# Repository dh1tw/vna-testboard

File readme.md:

# VNA Testboard PCB

I really like this small PCB testboard for prototyping and experimenting with my Vector Network Analyzers. [SDR-Kits](https://www.sdr-kits.net) used to sell it as a complimentary item for the DG8SAQ VNA. Unfortunately, mine showed some wear and SDR-Kits doesn't sell the PCB / Testkit anymore. So I clone it.

## Layout

## Design considerations

The PCB was designed in KiCad 7. You will most likely have to **change / adopt the SMA connectors** since I used a couple of non-standard ones which, I just had in stock.

I designed the traces as microstrip lines, matching 50 Ohm. This resulting trace width is 1.85mm using __1,0mm PCB thickness__ and an Epsilon r = 4.5 of the FR4 material. I get accurate results up to a few hundred Megahertz.

The pin sockets have a 2.54mm spacing.

I use Nylon M3 screws & nuts as feet.

## License

[Creative Commons Attribution-ShareAlike 4.0 International](https://creativecommons.org/licenses/by-sa/4.0/deed.en)

## This means you are free to:

- **Share** - copy and redistribute the material in any medium or format
- **Adapt** - remix, transform, and build upon the material for any purpose, even commercially

## under the following terms:

- **Attribution** - You must give appropriate credit, provide a link to the license, and indicate if changes were made. You may do so in any reasonable manner, but not in any way that suggests the licensor endorses you or your use.
- **ShareAlike** - If you remix, transform, or build upon the material, you must distribute your contributions under the same license as the original.

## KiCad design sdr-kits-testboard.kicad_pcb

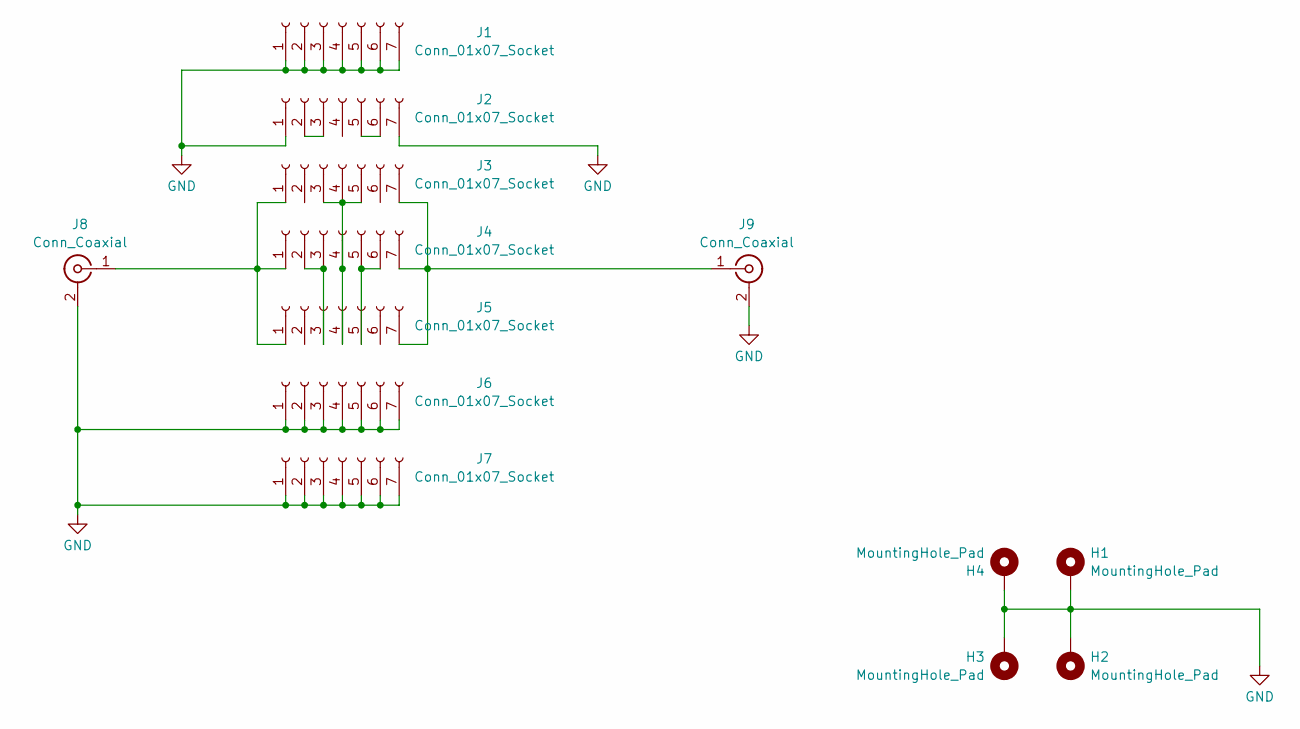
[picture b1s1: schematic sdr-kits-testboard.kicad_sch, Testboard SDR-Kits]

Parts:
H1, H2, H3, H4: MountingHole_Pad; MountingHole_3.2mm_M3_DIN965_Pad
J1, J2, J3, J4, J5, J6, J7: Conn_01x07_Socket; PinSocket_1x07_P2.54mm_Vertical_SDR-Kits
J8, J9: Conn_Coaxial; SMA_Aliexpress_EdgeMount

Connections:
GND: H1.1, H2.1, H3.1, H4.1, J1.1, J1.2, J1.3, J1.4, J1.5, J1.6, J1.7, J2.1, J2.7, J6.1, J6.2, J6.3, J6.4, J6.5, J6.6, J6.7, J7.1, J7.2, J7.3, J7.4, J7.5, J7.6, J7.7, J8.2 (Ext), J9.2 (Ext)
unnamed: J2.2, J2.3
unnamed: J2.5, J2.6
unnamed: J3.1, J4.1, J5.1, J8.1 (In)
unnamed: J3.3, J3.4, J3.5, J4.4, J5.4
unnamed: J3.7, J4.7, J5.7, J9.1 (In)
unnamed: J4.2, J4.3, J5.3
unnamed: J4.5, J4.6, J5.5

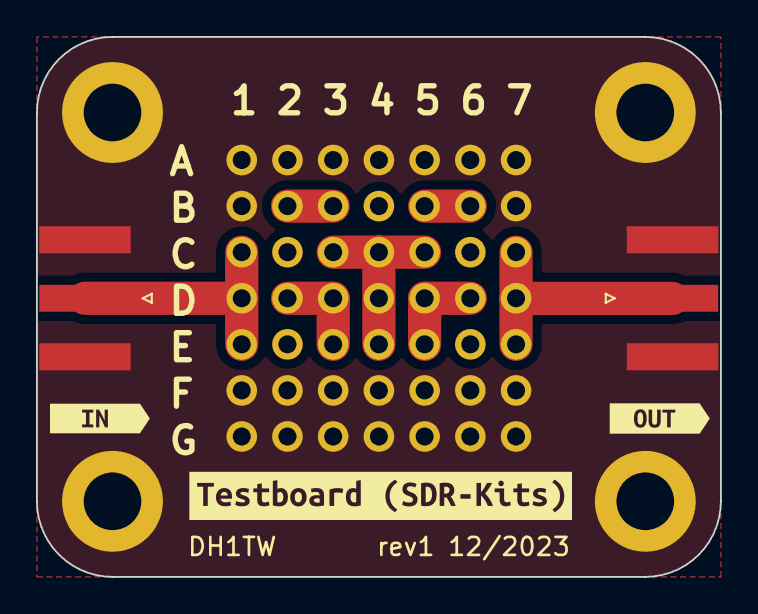
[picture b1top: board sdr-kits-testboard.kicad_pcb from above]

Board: 2 copper layers, 38.0 x 30.0 mm, 16 parts (0 on the bottom side), 8 nets.

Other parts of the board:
kibuzzard-6574F6D7: G***; kibuzzard-6574F6D7
kibuzzard-6574F6F3: G***; kibuzzard-6574F6F3
kibuzzard-6574F576: G***; kibuzzard-6574F576

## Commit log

2024-01-06 added comments about Spacers and Frequency
2024-01-28 described in readme the license
